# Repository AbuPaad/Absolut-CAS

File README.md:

<!-- boardrepo-badge:v1 -->

<!-- /boardrepo-badge:v1 -->
[PRODUCT WEBSITE](https://absolutcas.com)
# Absolut-CAS — the drop-in board

KiCad project for the NumOS Casio Port. It replaces the original board inside a stock Casio
fx-82 / fx-991 with an ESP32-S3, a colour screen interface and a oem compatible keypad matrix — reusing
the calculator's own shell and buttons.
> [!WARNING]
> **Schematics only — the PCB files in this repo are stale.**
> Every schematic (`*.kicad_sch`) here is current and complete. Every board file (`*.kicad_pcb`)
> is out of date: it does not match the last fabricated board and will not work as drawn. The PCB
> is being reworked and will be pushed here soon — do not fabricate from anything in `hardware/`
> until then.

---

## Components

- **U8 — ESP32-S3-WROOM-1**. Does everything/core MCU.
- **U7 — TCA9555DBR** (16-bit I²C expander, SSOP-24). Reads the keypad matrix, so the whole
  keypad costs the MCU two pins instead of fifteen.
- **S1 — 40-pin 0.5 mm FPC connector**. This is what the ILI9341 2.4" 320×240 panel plugs into.
- **U5 — TP4056-42-ESOP8.** Li-ion charge management for battery.
- **Q1 — DMP3099L** P-channel MOSFET, plus a battery protection pair on SOT-23. Power Path 
- **LDO — TPS73733DCQR.** Regulates the rails.
- **J2 — USB-C 16P connector**, USB 2.0 only, `5.1k` CC pull-downs on R3/R19.
- **J4 — JST PH 2-pin.** Battery connector.
- **J3 — Micro SD socket** (footprint `CONN_TF-01A_HRO`). Fitted. Doesn't work. See status.
- **B1/B2** — two tactile push buttons. **D5/D6** — LEDs. **D4** — 1N5819. **D1–D3** — SOD-123.
- Passives are all 0603.
- **Camera Header for an [OV2640 Module](https://www.amazon.com.au/Purpose-Modules-Compression-Applications-Streaming/dp/B0H9SBRZQX)
  - will use an [fpc-connector based smaller ov2640](https://www.alibaba.com/product-detail/TZ-Mini-OV2640-Camera-Module-CMOS_1601220633036.html?spm=a2700.prosearch.normal_offer.d_title.5f5e67af3gyMJ3&priceId=1afb448003314792b85f3ed40adf9f01) in v2 and have it embedded in unit rather than external.

## The board itself

- **4 layers**: `F.Cu`, `In1.Cu` (GND Plane), `In2.Cu` (signal), `B.Cu`
- 1.6 mm.
- **Outline: 65 × 94 mm** as drawn in the board file.
- **Every component sits on `B.Cu`** — the whole board mounts bottom-side-up behind the keypad.
## What it can actually do

- Runs NumOS: CAS maths, natural display, graphing, apps, and a Game Boy emulator.
- 320×240 colour screen instead of a 7-segment LCD.
- Wi-Fi on board. The AI and notes features need it.
- Rechargeable Li-ion over USB-C. Untethered.
- Keypad-only input. No touch.
- OTA firmware updates are the eventual goal.
- Drop-in: same shell, same buttons, same feel.

---

## Files

| Path | What it is |
|---|---|
| `Cfx-port.kicad_pro` | Project settings. |
| `Cfx-port.kicad_sch` | Root schematic. Just holds the three sheets. |
| `Cfx-port.kicad_pcb` | The board. 95 footprints. |
| `keypad.kicad_sch` | Keypad matrix and the TCA9555 expander. |
| `power-ic.kicad_sch` | Charger, LDO, protection, USB-C. |
| `esp32-s3-pinout.kicad_sch` | Module pinout and connectors. |
| `production/` | Fabrication output. Generated locally, not versioned. |
| `jlcpcb/` | Order output folder. `gerber/` and `production_files/` are **empty**. |
| `plots/` | `Cfx-port__Assembly.pdf`. |
| `packages3D/` | 3D models. `Downloads/` holds the vendor STEP files. |
| `Cfx-port-backups/` | Dated zips. The project's own footprints live here in `Library.pretty`. |
| `KicadConductivePads/` | Third-party pad footprints. Own LICENSE, own nested `.git`. |
| `.history/` | KiCad autosaves. Contains its own nested `.git`. |
| `.portability/` | KiCad's own backup manifest. |
| `DRC.rpt` / `ERC.rpt` | Design rule and electrical rule reports. |
| `Cfx-port-all-pos.csv` | Pick-and-place data. |
| `fp-lib-table` / `sym-lib-table` | Footprint and symbol library pointers. |
| `NeoFX.kicad_sym`, `sch_data.json`, `fp-info-cache`, `fabrication-toolkit-options.json` | Support and scratch. |
| `untitled.kicad_sch`, `Cfx-port.kicad_sch_old` | Old copies, not part of the project. |

Everything else in this folder is KiCad scratch — `~*.lck` locks, zero-byte `tmp*.rpt`,
`#auto_saved_files#`, `.step`, and `model.stl.[sS][tT][eE][pP]` (a broken filename from a shell
glob that got committed). Safe to ignore.

## Status — v1

- Board ordered **August 2026**, delivered, built, partly tested.
- **Working:** keypad, calculator maths, boot, Wi-Fi.
- **Broken:** the SD slot. Fitted and dead. Board decision 2026-10-01 — no SD in v1, it comes
  back in v2.
- This is a first PCB. Nothing here is physically validated beyond "it boots".
- v2 is roughly a month out. No promises.

## Known issues and cleanup before the next order

- **The reports are stale.** DRC and ERC are dated 2026-07-31 / 2026-08-02, older than the last
  board edit (2026-10-03). Re-run both before trusting them.
- Last DRC: 0 violations, but **59 unconnected pads**.
- Last ERC: 0 errors, 5 warnings — two library symbol mismatches and three power pins not driven
  by any output power pin.
---

## Credit

Keypad pad footprints come from **KicadConductivePads** by nataliethenerd — public domain
(Unlicense), sizing loosely based on the Game Boy Color and Pocket pads. Everything else in this
folder is AbuPaad's
Keypad pad footprints come from **KicadConductivePads** by nataliethenerd — public domain
(Unlicense), sizing loosely based on the Game Boy Color and Pocket pads. Everything else in this
folder is AbuPaad's

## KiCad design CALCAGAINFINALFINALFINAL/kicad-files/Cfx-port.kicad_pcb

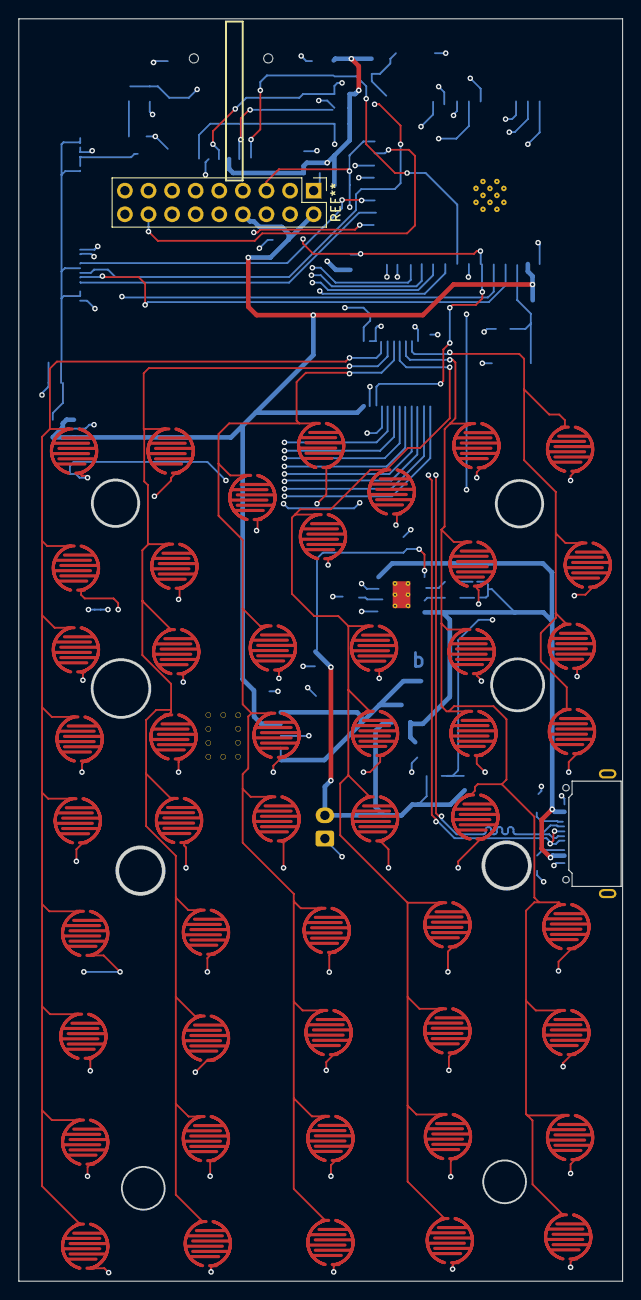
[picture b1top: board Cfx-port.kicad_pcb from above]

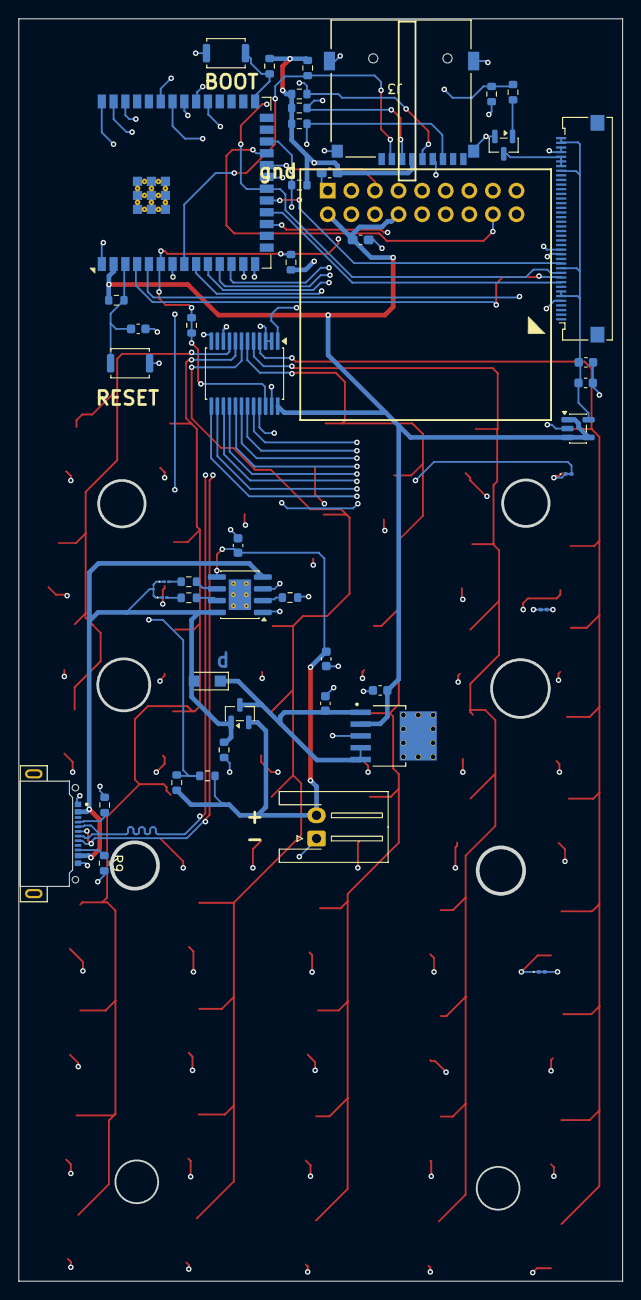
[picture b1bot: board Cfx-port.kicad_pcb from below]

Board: 4 copper layers, 65.0 x 135.9 mm, 96 parts (47 on the bottom side), 47 nets.

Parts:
B1, B2: SW_Push_SPST_NO_Alps_SKRK
C1, C1#2: 0.1; C_0603_1608Metric
C2: 10uf; C_0603_1608Metric
C5: 10µF; C_0603_1608Metric
C6, C6#2, C6#3: 1µF; C_0603_1608Metric
D1, D3, D6: D_0201_0603Metric
D8: 1N5819; Nexperia_CFP3_SOD-123W
D15, D15#2: LED; LED_01005_0402Metric
J2: USB_C_Receptacle_USB2.0_16P; TENSILITY_54-00304
J3: Micro_SD_Card; CONN_TF-01A_HRO
J4: Conn_01x02; JST_XH_S2B-XH-A-1_1x02_P2.50mm_Horizontal
LDO: IC_TPS73733DCQR
NIGERC: 100k; R_0603_1608Metric
Q1: DMP3099L; SOT-23
R1, R2, R3, R5#2, R55, R67, R123, R902: 10k; R_0603_1608Metric
R5: 4.7k; R_0603_1608Metric
R8, R9: 5.1k; R_0603_1608Metric
R10, R11, R67#2: 1k; R_0603_1608Metric
R12: 1.6; R_0603_1608Metric
S1: Omron_XF2M-4015-1A_1x40-1MP_P0.5mm_Horizontal
SOt-23: idk; SOT-23
SW49, SW52, SW55, SW56, SW57, SW58, SW59, SW60, SW61, SW62, SW63, SW64, SW65, SW66, SW67, SW68, SW69, SW70, SW71, SW72, SW73, SW74, SW75, SW76, SW77, SW78, SW79, SW80, SW81, SW82, SW83, SW84, SW85, SW86, SW87, SW88, SW89, SW90, SW91, SW92, SW93, SW94, SW95, SW96, SW97, SW98, SW99, SW100, SW101: SW_SPST; conductive pad
U1: TPS73125DBV; SOT-23-5
U5: TP4056-42-ESOP8; SOIC-8-1EP_3.9x4.9mm_P1.27mm_EP2.41x3.3mm_ThermalVias
U7: TCA9535DBR; SSOP-24_5.3x8.2mm_P0.65mm
U8: ESP32-S3-WROOM-2
cuba: 100k; R_0603_1608Metric
r21: 100k; R_0603_1608Metric
r2123: 4.7k; R_0603_1608Metric
toes1, toes4: 10uf; C_0603_1608Metric_Pad1.08x0.95mm_HandSolder

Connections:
2V8: C1#2.1, C2.1, S1.6, S1.7, S1.12, S1.33, S1.39, S1.40, U1.5 (OUT)
3V3: C6#2.2, J3.4 (VDD), LDO.2, R1.2, R2.2, R3.2, R5.1, R55.2, R123.2, R902.2, U1.1 (IN), U1.3 (EN), U1.4 (NR), U7.24 (VCC), U8.2 (3V3), r2123.1, toes1.2, toes4.1
/Keypad Matrix/C1: SW49.2 (B), SW52.2 (B), SW55.2 (B), SW56.2 (B), SW57.2 (B), SW58.2 (B), SW59.2 (B), SW60.2 (B), SW61.2 (B), U7.4 (P00)
/Keypad Matrix/C2: SW62.2 (B), SW63.2 (B), SW64.2 (B), SW65.2 (B), SW66.2 (B), SW67.2 (B), SW68.2 (B), SW69.2 (B), SW70.2 (B), U7.5 (P01)
/Keypad Matrix/C3: SW71.2 (B), SW72.2 (B), SW73.2 (B), SW74.2 (B), SW75.2 (B), SW76.2 (B), SW77.2 (B), SW78.2 (B), SW79.2 (B), U7.6 (P02)
/Keypad Matrix/C4: SW80.2 (B), SW81.2 (B), SW82.2 (B), SW83.2 (B), SW84.2 (B), SW85.2 (B), SW86.2 (B), SW87.2 (B), SW88.2 (B), U7.7 (P03)
/Keypad Matrix/C5: SW89.2 (B), SW90.2 (B), SW91.2 (B), SW92.2 (B), SW93.2 (B), SW94.2 (B), SW95.2 (B), SW96.2 (B), SW97.2 (B), U7.8 (P04)
/Keypad Matrix/C6: SW98.2 (B), SW99.2 (B), SW100.2 (B), SW101.2 (B), U7.9 (P05)
/Keypad Matrix/R1: D1.1, D1.2, SW49.1 (A), SW62.1 (A), SW71.1 (A), SW80.1 (A), SW89.1 (A), SW98.1 (A), U7.10 (P06)
/Keypad Matrix/R2: D3.1, D3.2, SW52.1 (A), SW63.1 (A), SW72.1 (A), SW81.1 (A), SW90.1 (A), SW99.1 (A), U7.13 (P10)
/Keypad Matrix/R3: SW55.1 (A), SW64.1 (A), SW73.1 (A), SW82.1 (A), SW91.1 (A), SW100.1 (A), U7.14 (P11)
/Keypad Matrix/R4: SW56.1 (A), SW65.1 (A), SW74.1 (A), SW83.1 (A), SW92.1 (A), SW101.1 (A), U7.15 (P12)
/Keypad Matrix/R5: SW57.1 (A), SW66.1 (A), SW75.1 (A), SW84.1 (A), SW93.1 (A), U7.16 (P13)
/Keypad Matrix/R6: D6.1, D6.2, SW58.1 (A), SW67.1 (A), SW76.1 (A), SW85.1 (A), SW94.1 (A), U7.17 (P14)
/Keypad Matrix/R7: SW59.1 (A), SW68.1 (A), SW77.1 (A), SW86.1 (A), SW95.1 (A), U7.18 (P15)
/Keypad Matrix/R8: SW60.1 (A), SW69.1 (A), SW78.1 (A), SW87.1 (A), SW96.1 (A), U7.19 (P16)
/Keypad Matrix/R9: SW61.1 (A), SW70.1 (A), SW79.1 (A), SW88.1 (A), SW97.1 (A), U7.20 (P17)
/esp32-s3 pinout/CMD: J3.3 (CMD), R1.1, U8.32 (IO39)
/esp32-s3 pinout/CS: S1.9, U8.18 (IO10)
/esp32-s3 pinout/CS1: J3.2 (DAT3/CD), R3.1, U8.8 (IO15)
/esp32-s3 pinout/DC: S1.10, U8.4 (IO4)
/esp32-s3 pinout/MISO: J3.7 (DAT0), R2.1, U8.21 (IO13)
/esp32-s3 pinout/RST: S1.15, U8.5 (IO5)
/esp32-s3 pinout/SCK: J3.5 (CLK), R902.1, S1.11, U8.20 (IO12)
/esp32-s3 pinout/cathode: S1.34, S1.35, S1.36, SOt-23.3 (D)
/power-ic/BAT+: C5.2, C6.2, J4.2, Q1.2 (S), U5.5 (BAT), cuba.2, r21.2
/power-ic/PROG: R12.1, U5.2 (PROG)
BL: R67.2, R67#2.2, U8.35 (IO42)
BL1: R67#2.1, SOt-23.1 (G)
GND: B1.2, B2.2, C1.2, C1#2.2, C2.2, C5.1, C6.1, C6#2.1, C6#3.1, J2.C1 (SBU1_A8), J2.C12 (D+_A6), J2.S1 (SHIELD_SH), J2.S2 (SHIELD_SH), J3.6 (VSS), J3.MNT1, J3.MNT2, J3.MNT3, J3.MNT4, J4.1, LDO.3, LDO.6, LDO.7, LDO.8, LDO.9, LDO.10, LDO.11, LDO.12, LDO.13, LDO.14, LDO.15, LDO.16, NIGERC.1, R8.2, R9.2, R12.2, R67.1, S1.5, S1.16, S1.37, S1.38, SOt-23.2 (S), U1.2 (GND), U5.1 (TEMP), U5.3 (GND), U5.9 (EPAD), U7.2 (A1), U7.3 (A2), U7.12 (GND), U7.21 (A0), U8.1 (GND), U8.40 (GND), U8.41 (GND), toes1.1, toes4.2
MOSI: S1.13, U8.19 (IO11)
unnamed: D15#2.2 (A), R10.1
unnamed: D15.2 (A), R11.1
unnamed: J2.C4 (VBUS_B4), R8.1
unnamed: J2.C10 (GND_A1), R9.1
unnamed: R10.2, U5.7 (~CHRG)
unnamed: R11.2, U5.6 (~STDBY)
SCL: R5#2.1, R5#2.2, U7.22 (SCL), U8.6 (IO6), r2123.2
SDA: R5.2, U7.23 (SDA), U8.24 (IO47)
VCC: D8.2 (A), D15.1 (K), D15#2.1 (K), J2.C2 (GND_B1), J2.C11 (CC1_A5), NIGERC.2, Q1.1 (G), U5.4 (V_{CC}), U5.8 (CE)
batprog: U8.7 (IO7), cuba.1, r21.1
boot: B1.1, R55.1, U8.27 (IO0)
en: B2.1, C1.1, R123.1, U8.3 (EN)
pwr: C6#3.2, D8.1 (K), LDO.1, LDO.4, LDO.5, Q1.3 (D)
usb_N: J2.C5 (GND_A12), J2.C7 (D-_A7), U8.13 (USB_D-)
usb_P: J2.C6 (VBUS_A9), J2.C8 (CC2_B5), U8.14 (USB_D+)
~INT: U7.1 (~INT), U8.22 (IO14)

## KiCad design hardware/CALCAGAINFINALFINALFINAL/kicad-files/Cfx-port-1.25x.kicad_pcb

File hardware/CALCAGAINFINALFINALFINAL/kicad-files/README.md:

# Cfx-port — the drop-in board

KiCad project for the NumOS drop-in PCB. It replaces the original board inside a stock Casio
fx-82 / fx-991 with an ESP32-S3, a colour screen interface and a proper keypad matrix — reusing
the calculator's own shell and buttons.

Firmware lives in `../../../firmware/AbsolutOS`. This folder is the hardware.

> [!WARNING]
> **Schematics only — the PCB files in this repo are stale.**
> Every schematic (`*.kicad_sch`) here is current and complete. Every board file (`*.kicad_pcb`)
> is out of date: it does not match the last fabricated board and will not work as drawn. The PCB
> is being reworked and will be pushed here soon — do not fabricate from anything in this folder
> until then.

---

## Components

- **U8 — ESP32-S3-WROOM-2** (LCSC `C2913202`). Does everything: keypad scanning, screen, Wi-Fi.
- **U7 — TCA9555DBR** (16-bit I²C expander, SSOP-24). Reads the keypad matrix, so the whole
  keypad costs the MCU two pins instead of fifteen.
- **S1 — 40-pin 0.5 mm FPC connector** (`CONN40_AFC01-S40FCA-00_JUS`; Omron `XF2M-4015-1A` in the
  symbol library). This is what the ILI9341 3.2" 320×240 panel plugs into. The panel itself is
  not on this board.
- **U5 — TP4056-42-ESOP8.** Li-ion charge management off the USB-C port.
- **Q1 — DMP3099L** P-channel MOSFET, plus a battery protection pair on SOT-23 (the two parts
  still valued `idk` in the schematic — they exist, they just were never named).
- **LDO — TPS73733DCQR.** Regulates the rails.
- **J2 — USB-C 16P receptacle**, USB 2.0 only, `5.1k` CC pull-downs on R3/R19.
- **J4 — JST PH 2-pin.** Battery connector.
- **J3 — Micro SD socket** (footprint `CONN_TF-01A_HRO`). Fitted. Doesn't work. See status.
- **B1/B2** — two tactile push buttons. **D5/D6** — LEDs. **D4** — 1N5819. **D1–D3** — SOD-123.
- Passives are all 0603.
- **No camera and no expansion header on this revision.** `sym-lib-table` points at an OV2640
  symbol library sitting in somebody's Downloads folder, but nothing from it is placed.

## The board itself

- **4 layers**: `F.Cu`, `In1.Cu` (power), `In2.Cu` (signal), `B.Cu`. The inner layers are
  actually routed — this is not a 2-layer board with the inner layers declared and unused.
- 1.6 mm.
- **Outline: 65 × 136 mm** as drawn in the board file.
- **Every component sits on `B.Cu`** — the whole board mounts bottom-side-up behind the keypad.
- Last DRC run: **0 violations**. Detail in the reports section below.

## What it can actually do

- Runs NumOS: CAS maths, natural display, graphing, apps, and a Game Boy emulator.
- A real 320×240 colour screen instead of a 7-segment LCD.
- Wi-Fi on board. The AI and notes features need it.
- Rechargeable Li-ion over USB-C. Untethered.
- Keypad-only input. No touch.
- OTA firmware updates are the eventual goal.
- Drop-in: same shell, same buttons, same feel.

---

## Files

| Path | What it is |
|---|---|
| `Cfx-port.kicad_pro` | Project settings. |
| `Cfx-port.kicad_sch` | Root schematic. Just holds the three sheets. |
| `Cfx-port.kicad_pcb` | The board. 95 footprints. |
| `keypad.kicad_sch` | Keypad matrix and the TCA9555 expander. |
| `power-ic.kicad_sch` | Charger, LDO, protection, USB-C. |
| `esp32-s3-pinout.kicad_sch` | Module pinout and connectors. |
| `production/` | Fabrication output. Generated locally, not versioned — see below. |
| `jlcpcb/` | Order output folder. `gerber/` and `production_files/` are **empty**. |
| `plots/` | `Cfx-port__Assembly.pdf`. |
| `packages3D/` | 3D models. `Downloads/` holds the vendor STEP files. |
| `Cfx-port-backups/` | Dated zips. The project's own footprints live here in `Library.pretty`. |
| `KicadConductivePads/` | Third-party pad footprints. Own LICENSE, own nested `.git`. |
| `.history/` | KiCad autosaves. Contains its own nested `.git`. |
| `.portability/` | KiCad's own backup manifest. |
| `DRC.rpt` / `ERC.rpt` | Design rule and electrical rule reports. |
| `Cfx-port-all-pos.csv` | Pick-and-place data. |
| `fp-lib-table` / `sym-lib-table` | Footprint and symbol library pointers. |
| `NeoFX.kicad_sym`, `sch_data.json`, `fp-info-cache`, `fabrication-toolkit-options.json` | Support and scratch. |
| `untitled.kicad_sch`, `Cfx-port.kicad_sch_old` | Old copies, not part of the project. |

Everything else in this folder is KiCad scratch — `~*.lck` locks, zero-byte `tmp*.rpt`,
`#auto_saved_files#`, `.step`, and `model.stl.[sS][tT][eE][pP]` (a broken filename from a shell
glob that got committed). Safe to ignore.

### Fabrication outputs

`production/` is a local scratch directory for fabrication output — gerbers, BOM, pick-and-place,
packaged zips. It is **not versioned** (`.gitignore`), and the v1 packaged set (`Cfx-port.zip`)
has been deleted. What is on disk here was generated for the v1 board and does not match the
current board design; regenerate before ordering.

Readable versions live one level up: `../Docs/Matrix.pdf` for the keypad matrix drawing,
`../../../Docs/schematic.pdf` for the flattened schematic, and `../../../Reference/` for the
vendor datasheets.

---

## Status — v1

- Board ordered **August 2026**, delivered, built and running.
- **Working:** display, keypad, boot, calculator maths and graphing, the Game Boy emulator, the
  new Casio font, Wi-Fi.
- The display was DOA on the first build and has since been fixed.
- **Broken:** the SD slot, and only that. Fitted and dead. Board decision 2026-10-01 — no SD in
  v1, it comes back in v2.
- v2 is roughly a month out.

## Known issues and cleanup before the next order

- **The reports are stale.** DRC and ERC are dated 2026-07-31 / 2026-08-02, older than the last
  board edit (2026-10-03). Re-run both before trusting them.
- Last DRC: 0 violations, but **59 unconnected pads**.
- Last ERC: 0 errors, 5 warnings — two library symbol mismatches and three power pins not driven
  by any output power pin.
- **Two footprints are still unannotated** (`REF**`) and two SOT-23 parts are valued `idk`.
  Real parts, never named.
- **No title block in the project**, so no revision or date is stamped anywhere in the files.
- **`U7` is a `TCA9555DBR`, but the schematic symbol and the BOM line still read
  `TCA9535DBR`.** The 9535 and 9555 are pin-compatible siblings, so it works, but the BOM should
  name the part actually fitted before it goes out again.
- `bom.csv` and `designators.csv` still list **J3** even though the current board file does not
  place its footprint. The two have drifted apart.
- **`sym-lib-table` points at absolute paths** (`/home/fih/Downloads/...`). This breaks for
  anyone who is not on that machine. Fix before publishing.
- `fp-lib-table` points the `Library` entry at `Cfx-port-backups/Library.pretty`. The project's
  own footprints sitting in a backups folder is fragile.
- The firmware repo keeps its own hardware contract
  (`../../../firmware/AbsolutOS/docs/PRODUCTION_PCBA_HARDWARE_CONTRACT.md`). That document is
  written against a different revision and disagrees with the files here on the module
  (`WROOM-1U` vs `WROOM-2`) and the layer count (two-layer vs four). **The files in this folder
  are current.**

---

## Credit

Keypad pad footprints come from **KicadConductivePads** by nataliethenerd — public domain
(Unlicense), sizing loosely based on the Game Boy Color and Pocket pads. Everything else in this
folder is AbuPaad's.

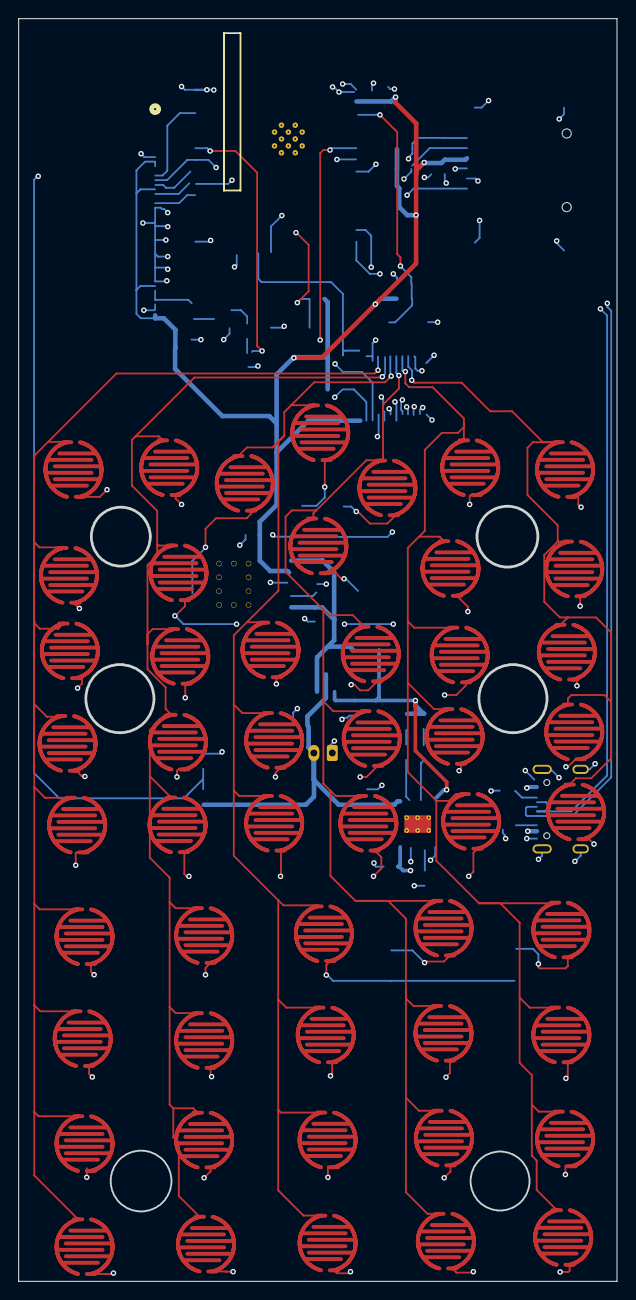
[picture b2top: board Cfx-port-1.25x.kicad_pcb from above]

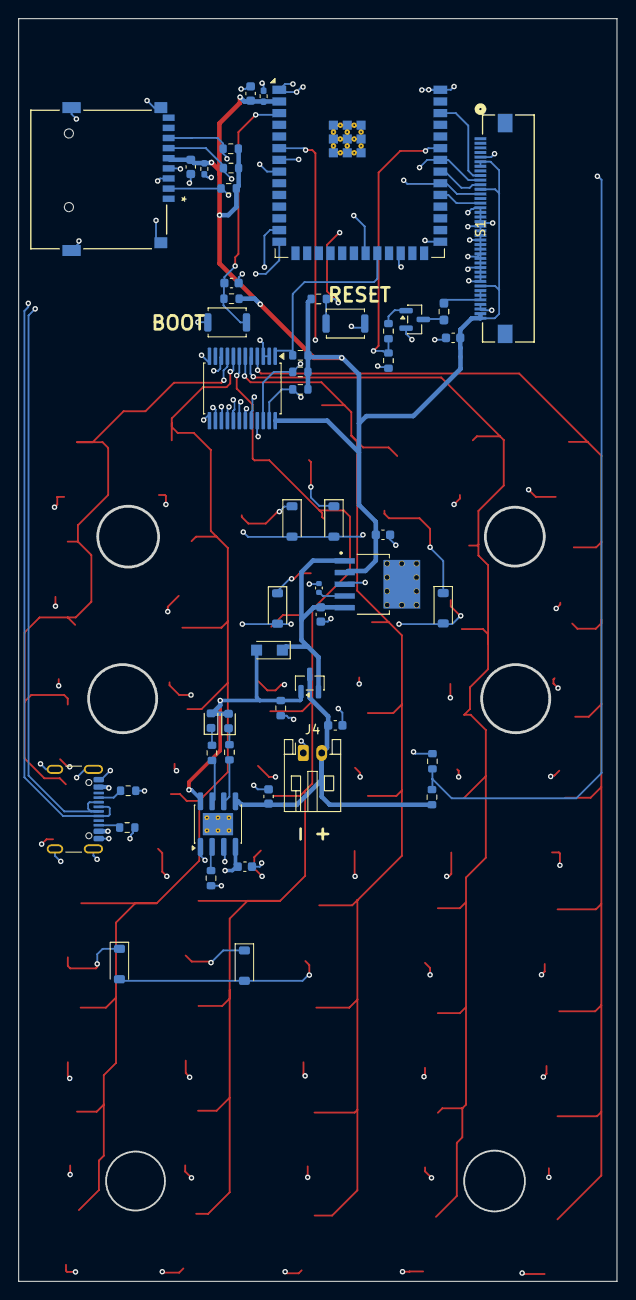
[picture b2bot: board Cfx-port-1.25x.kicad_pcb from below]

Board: 4 copper layers, 65.0 x 137.2 mm, 103 parts (53 on the bottom side), 54 nets.

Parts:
B1, B2: SW_Push_SPST_NO_Alps_SKRK
C1: 0.1; C_0603_1608Metric
C2: 10uf; C_0603_1608Metric
C3, C5, C7, C412: 10µF; C_0603_1608Metric
C4, C6, C8: 1µF; C_0603_1608Metric
D0, D1, D2, D3, D7, D8: D_SOD-123
D4: 1N5819; Nexperia_CFP3_SOD-123W
D5, D6: LED; D_0603_1608Metric
J2: USB_C_Receptacle_USB2.0_16P; USB_C_Receptacle_GCT_USB4105-xx-A_16P_TopMnt_Horizontal
J4: Conn_01x02; JST_PH_S2B-PH-K_1x02_P2.00mm_Horizontal
LDO: IC_TPS73733DCQR
Q1: DMP3099L; SOT-23
R1, R2: 1k; R_0603_1608Metric
R3: 5.1k; R_0603_1608Metric
R6, R7, R8, R9, R10: 10k; R_0603_1608Metric
R12: 2.4k; R_0603_1608Metric
R17: 510; R_0603_1608Metric
R20: 4.7k; R_0603_1608Metric
S1: CONN40_AFC01-S40FCA-00_JUS
SOt-23: idk; SOT-23
SW49, SW52, SW55, SW56, SW57, SW58, SW59, SW60, SW61, SW62, SW63, SW64, SW65, SW66, SW67, SW68, SW69, SW70, SW71, SW72, SW73, SW74, SW75, SW76, SW77, SW78, SW79, SW80, SW81, SW82, SW83, SW84, SW85, SW86, SW87, SW88, SW89, SW90, SW91, SW92, SW93, SW93#2, SW94, SW95, SW96, SW97, SW98, SW99, SW100, SW101: SW_SPST; conductive pad
U5: TP4056-42-ESOP8; SOIC-8-1EP_3.9x4.9mm_P1.27mm_EP2.41x3.3mm_ThermalVias
U7: TCA9555DBR; SSOP-24_5.3x8.2mm_P0.65mm
U8: ESP32-S3-WROOM-1; ESP32-S3-WROOM-2
c12: 100nf; R_0402_1005Metric_Pad0.72x0.64mm_HandSolder
cat1: 100nf; R_0402_1005Metric_Pad0.72x0.64mm_HandSolder
netj: NetTie-2_SMD_Pad0.5mm
r11, r12, r15, r18: 10k; R_0603_1608Metric
r14, r16: 100k; R_0603_1608Metric
r19: 5.1k; R_0603_1608Metric
res: 10nf 0402; C_0402_1005Metric
rnein: 20ohm; R_0603_1608Metric_Pad0.98x0.95mm_HandSolder
toes: dw a; CONN_TF-01A_HRO

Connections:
2V8: C2.1, S1.6, S1.7, S1.12, S1.33, S1.39, S1.40, netj.2
3V3: C5.2, C7.2, C8.2, LDO.2, R6.2, R7.1, R8.2, R9.2, R10.2, R20.1, U7.24 (VCC), U8.2 (3V3), c12.1, cat1.1, netj.1, r12.2, r18.2, toes.5
/Keypad Matrix/C1: SW49.2 (B), SW52.2 (B), SW55.2 (B), SW56.2 (B), SW57.2 (B), SW58.2 (B), SW59.2 (B), SW60.2 (B), SW61.2 (B), U7.4 (P00)
/Keypad Matrix/C2: SW62.2 (B), SW63.2 (B), SW64.2 (B), SW65.2 (B), SW66.2 (B), SW67.2 (B), SW68.2 (B), SW69.2 (B), SW70.2 (B), U7.5 (P01)
/Keypad Matrix/C3: SW71.2 (B), SW72.2 (B), SW73.2 (B), SW74.2 (B), SW75.2 (B), SW76.2 (B), SW77.2 (B), SW78.2 (B), SW79.2 (B), U7.6 (P02)
/Keypad Matrix/C4: SW80.2 (B), SW81.2 (B), SW82.2 (B), SW83.2 (B), SW84.2 (B), SW85.2 (B), SW86.2 (B), SW87.2 (B), SW88.2 (B), U7.7 (P03)
/Keypad Matrix/C5: SW89.2 (B), SW90.2 (B), SW91.2 (B), SW92.2 (B), SW93#2.2 (B), SW94.2 (B), SW95.2 (B), SW96.2 (B), SW97.2 (B), U7.8 (P04)
/Keypad Matrix/C6: SW93.2 (B), SW98.2 (B), SW99.2 (B), SW100.2 (B), SW101.2 (B), U7.9 (P05)
/Keypad Matrix/R1: D0.2, D1.2, SW49.1 (A), SW62.1 (A), SW89.1 (A), SW98.1 (A), U7.10 (P06)
/Keypad Matrix/R2: D2.2, D8.2, SW52.1 (A), SW63.1 (A), SW90.1 (A), SW99.1 (A), U7.13 (P10)
/Keypad Matrix/R3: SW55.1 (A), SW64.1 (A), SW73.1 (A), SW82.1 (A), SW91.1 (A), SW100.1 (A), U7.14 (P11)
/Keypad Matrix/R4: SW56.1 (A), SW65.1 (A), SW74.1 (A), SW83.1 (A), SW92.1 (A), SW101.1 (A), U7.15 (P12)
/Keypad Matrix/R5: SW57.1 (A), SW66.1 (A), SW75.1 (A), SW84.1 (A), SW93.1 (A), SW93#2.1 (A), U7.16 (P13)
/Keypad Matrix/R6: D3.2, D7.2, SW58.1 (A), SW67.1 (A), SW76.1 (A), U7.17 (P14)
/Keypad Matrix/R7: SW59.1 (A), SW68.1 (A), SW77.1 (A), SW86.1 (A), SW95.1 (A), U7.18 (P15)
/Keypad Matrix/R8: SW60.1 (A), SW69.1 (A), SW78.1 (A), SW87.1 (A), SW96.1 (A), U7.19 (P16)
/Keypad Matrix/R9: SW61.1 (A), SW70.1 (A), SW79.1 (A), SW88.1 (A), SW97.1 (A), U7.20 (P17)
/esp32-s3 pinout/CS: S1.9, U8.38 (IO2)
/esp32-s3 pinout/CS1: R10.1, U8.8 (IO15), toes.7
/esp32-s3 pinout/DC: S1.11, U8.33 (IO40)
/esp32-s3 pinout/MISO: R6.1, U8.21 (IO13), toes.2
/esp32-s3 pinout/RST: S1.15, U8.31 (IO38)
/esp32-s3 pinout/SCK: S1.10, U8.34 (IO41), toes.4
/esp32-s3 pinout/cathode: S1.34, S1.35, S1.36, rnein.1
/power-ic/BAT+: C3.2, C6.2, J4.2, Q1.3 (D), U5.5 (BAT), r16.2
/power-ic/PROG: R12.1, U5.2 (PROG)
BL: R17.2, U8.35 (IO42), r11.2
BL1: R17.1, SOt-23.1 (G)
GND: B1.2, B2.2, C1.2, C2.2, C3.1, C4.1, C5.1, C6.1, C7.1, C8.1, C412.1, J2.A1, J2.A12 (GND_A12), J2.B1 (GND_B12), J2.B12 (GND_B1), J2.SH (SHIELD_SH), J4.1, LDO.3, LDO.6, LDO.7, LDO.8, LDO.9, LDO.10, LDO.11, LDO.12, LDO.13, LDO.14, LDO.15, LDO.16, R3.2, R12.2, S1.5, S1.16, S1.17, S1.18, S1.19, S1.20, S1.21, S1.22, S1.23, S1.24, S1.25, S1.26, S1.27, S1.28, S1.29, S1.30, S1.31, S1.32, S1.37, S1.38, SOt-23.2 (S), U5.1 (TEMP), U5.3 (GND), U5.9 (EPAD), U7.2 (A1), U7.3 (A2), U7.12 (GND), U7.21 (A0), U8.1 (GND), U8.40 (GND), U8.41 (GND), c12.2, cat1.2, r11.1, r14.2, r15.1, r19.2, res.2, toes.3, toes.MNT1, toes.MNT2, toes.MNT3, toes.MNT4
MOSI: R9.1, S1.13, U8.32 (IO39), toes.6
NR: LDO.4, res.1
unnamed: D5.1 (K), R1.1
unnamed: D6.1 (K), R2.1
unnamed: J2.A5, r19.1
unnamed: J2.B5 (CC1_A5), R3.1
unnamed: R1.2, U5.7 (~CHRG)
unnamed: R2.2, U5.6 (~STDBY)
R1D1: D1.1, SW71.1 (A)
R1D2: D0.1, SW80.1 (A)
R2D1: D8.1, SW72.1 (A)
R2D2: D2.1, SW81.1 (A)
R6D1: D7.1, SW94.1 (A)
SCL: R20.2, U7.22 (SCL), U8.6 (IO6)
SDA: R7.2, U7.23 (SDA), U8.24 (IO47)
VCC: C412.2, D4.2 (A), D5.2 (A), D6.2 (A), J2.A4, J2.A9 (VBUS_A9), J2.B4 (GND_A1), J2.B9 (SBU1_A8), Q1.1 (G), U5.4 (V_{CC}), U5.8 (CE), r15.2
batprog: U8.7 (IO7), r14.1, r16.1
boot: B1.1, U8.27 (IO0), r12.1
catode: SOt-23.3 (D), rnein.2
en: B2.1, C1.1, R8.1, U8.3 (EN)
pwr: C4.2, D4.1 (K), LDO.1, LDO.5, Q1.2 (S)
r6d2: D3.1, SW85.1 (A)
usb_N: J2.A7 (CC2_B5), J2.B7 (VBUS_B9), U8.13 (USB_D-)
usb_P: J2.A6, J2.B6 (D+_A6), U8.14 (USB_D+)
~INT: U7.1 (~INT), U8.22 (IO14), r18.1
